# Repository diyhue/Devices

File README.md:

# Devices
DIY Sensors and Controllers with support for diyHue

Documentation and instructions can be found at [diyhue.readthedocs.io](https://diyhue.readthedocs.io/en/latest/AddFuncts/index.html)!

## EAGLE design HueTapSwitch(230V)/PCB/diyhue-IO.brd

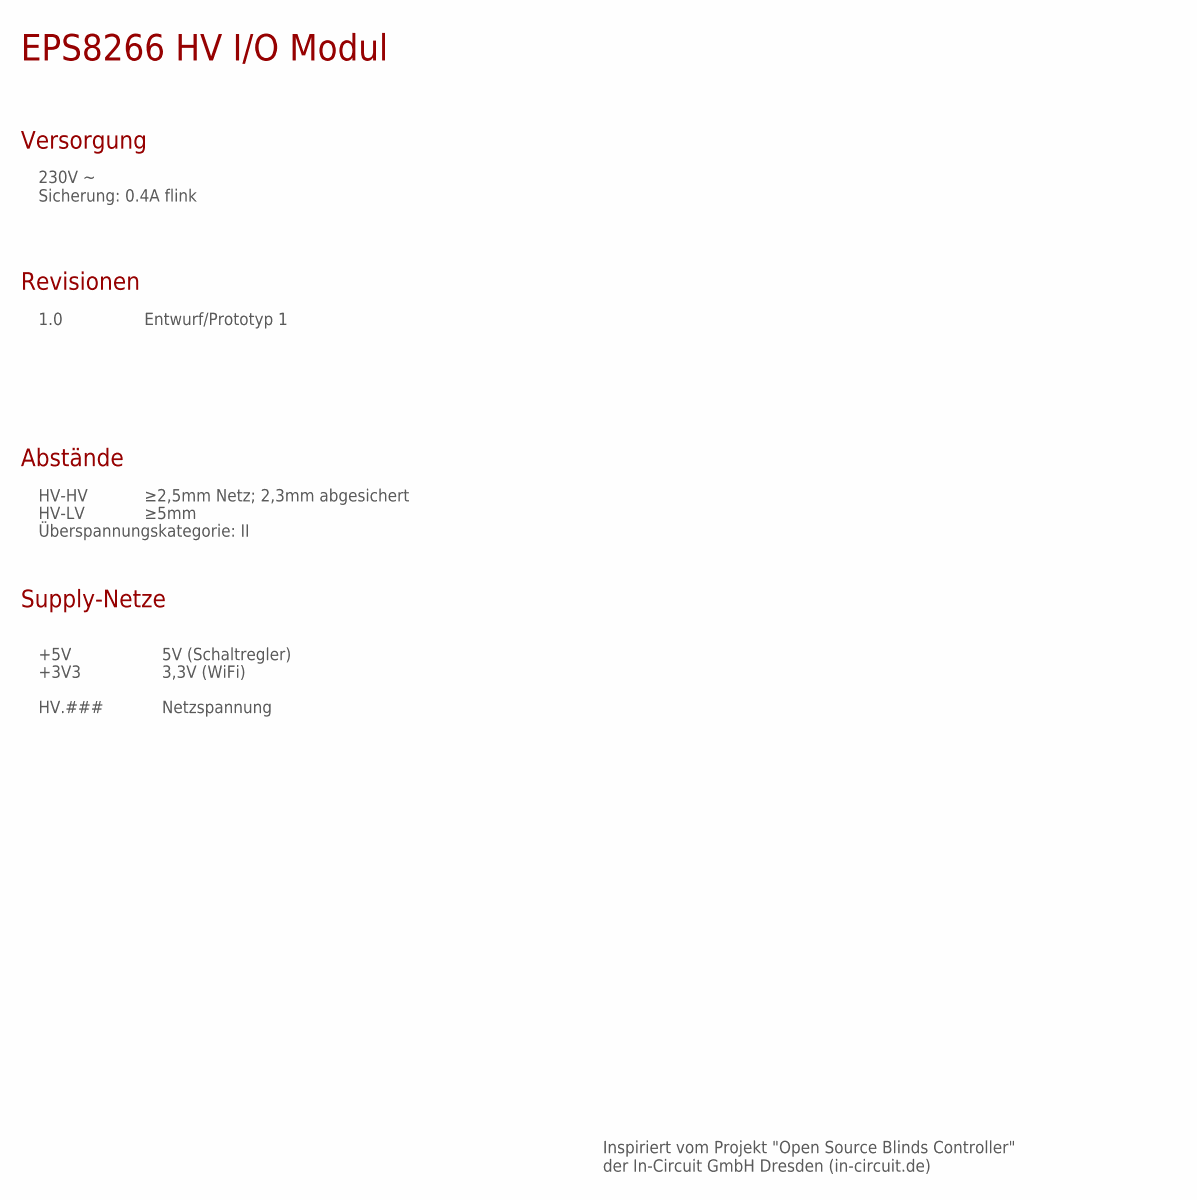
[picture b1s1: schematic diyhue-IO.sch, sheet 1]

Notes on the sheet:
Versorgung
Revisionen
1.0
Entwurf/Prototyp 1
230V ~ Sicherung: 0.4A flink
Supply-Netze
+3V3
+5V
5V (Schaltregler)
3,3V (WiFi)
Inspiriert vom Projekt "Open Source Blinds Controller" der In-Circuit GmbH Dresden (in-circuit.de)
Abstände
HV-HV
HV-LV
≥2,5mm Netz; 2,3mm abgesichert
≥5mm
Überspannungskategorie: II
HV.###
Netzspannung

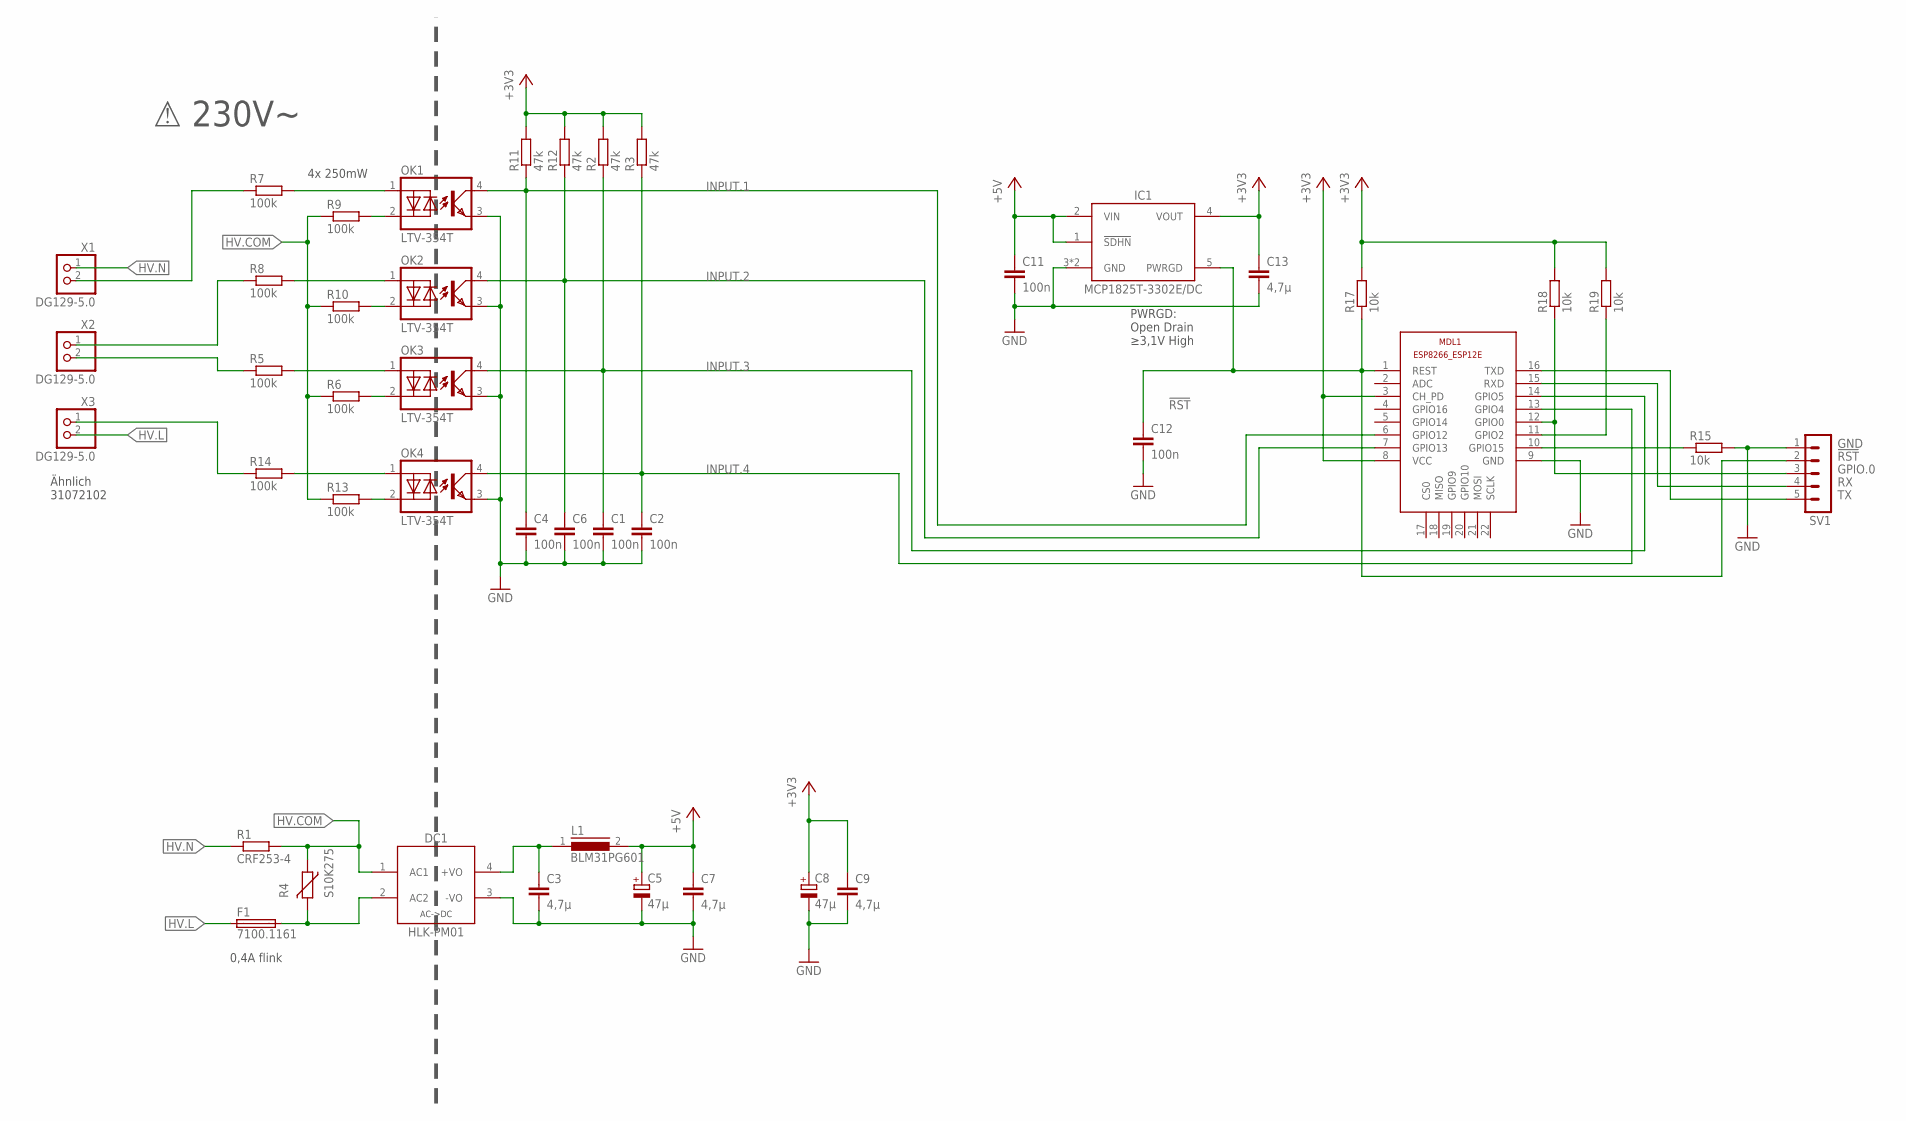
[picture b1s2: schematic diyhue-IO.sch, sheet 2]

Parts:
C1, C2, C4, C6, C11, C12: 100n; C0805K
C3, C7, C9, C13: 4,7µ; C0805K
C5, C8: 47µ; E2-5
DC1: HLK-PM01; HLK_PM01
F1: 7100.1161; SCHURTER_FRT250
IC1: MCP1825T-3302E/DC; SOT-223/5
L1: BLM31PG601; BLM31P
MDL1: ESP8266-12EESP8266-ESP12E; ESP8266-ESP12E
OK1, OK2, OK3, OK4: LTV-354T; LITEON_LTV-354
R1: CRF253-4; 0414V
R2, R3, R11, R12: 47k; R0805W
R4: S10K275; EPCOS_S10K275
R5, R6, R7, R8, R9, R10, R13, R14: 100k; R1210
R15, R17, R18, R19: 10k; R0805W
SV1: MA05-1
X1, X2, X3: DG129-5.0; 31012102

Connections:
!RST: C12.1, IC1.5 (PWRGD), MDL1.1 (REST), R17.1, SV1.2
+3V3: C8.+, C9.1, C13.1, IC1.4 (VOUT), MDL1.3 (CH_PD), MDL1.8 (VCC), R2.2, R3.2, R11.2, R12.2, R17.2, R18.2, R19.2
+5V: C5.+, C7.1, C11.1, IC1.1 (!SDHN), IC1.2 (VIN), L1.2
GND: C1.2, C2.2, C3.2, C4.2, C5.-, C6.2, C7.2, C8.-, C9.2, C11.2, C12.2, C13.2, DC1.3 (-VO), IC1.3 (GND), IC1.6 (GND), MDL1.9 (GND), OK1.3 (E), OK2.3 (E), OK3.3 (E), OK4.3 (E), R15.2, SV1.1
GPIO.0: MDL1.12 (GPIO0), R18.1, SV1.3
GPIO.2: MDL1.11 (GPIO2), R19.1
GPIO.15: MDL1.10 (GPIO15), R15.1
HV.COM: DC1.1 (AC1), R1.2, R4.1, R6.1, R9.1, R10.1, R13.1
HV.IN1: R7.1, X1.2
HV.IN2: R8.1, X2.1
HV.L: F1.1, X3.2
HV.N: R1.1, X1.1
HV.OUT1: R5.1, X2.2
HV.OUT2: R14.1, X3.1
INPUT.1: C4.1, MDL1.6 (GPIO12), OK1.4 (C), R11.1
INPUT.2: C6.1, MDL1.7 (GPIO13), OK2.4 (C), R12.1
INPUT.3: C1.1, MDL1.14 (GPIO5), OK3.4 (C), R2.1
INPUT.4: C2.1, MDL1.13 (GPIO4), OK4.4 (C), R3.1
unnamed: C3.1, DC1.4 (+VO), L1.1
unnamed: DC1.2 (AC2), F1.2, R4.2
unnamed: OK3.2 (CA), R6.2
unnamed: OK4.2 (CA), R13.2
unnamed: OK4.1 (AC), R14.2
unnamed: OK1.2 (CA), R9.2
unnamed: OK2.2 (CA), R10.2
unnamed: OK1.1 (AC), R7.2
unnamed: OK2.1 (AC), R8.2
unnamed: OK3.1 (AC), R5.2
RX: MDL1.15 (RXD), SV1.4
TX: MDL1.16 (TXD), SV1.5

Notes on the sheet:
Ähnlich 31072102
4x 250mW
0,4A flink
⚠ 230V~
PWRGD: Open Drain ≥3,1V High

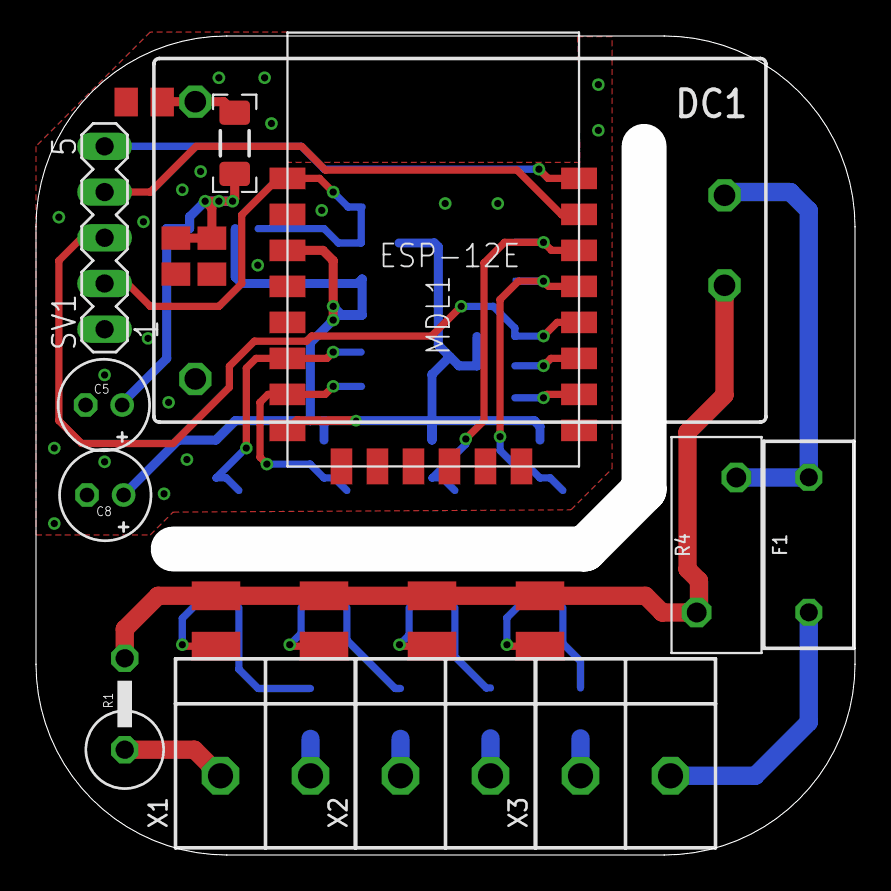
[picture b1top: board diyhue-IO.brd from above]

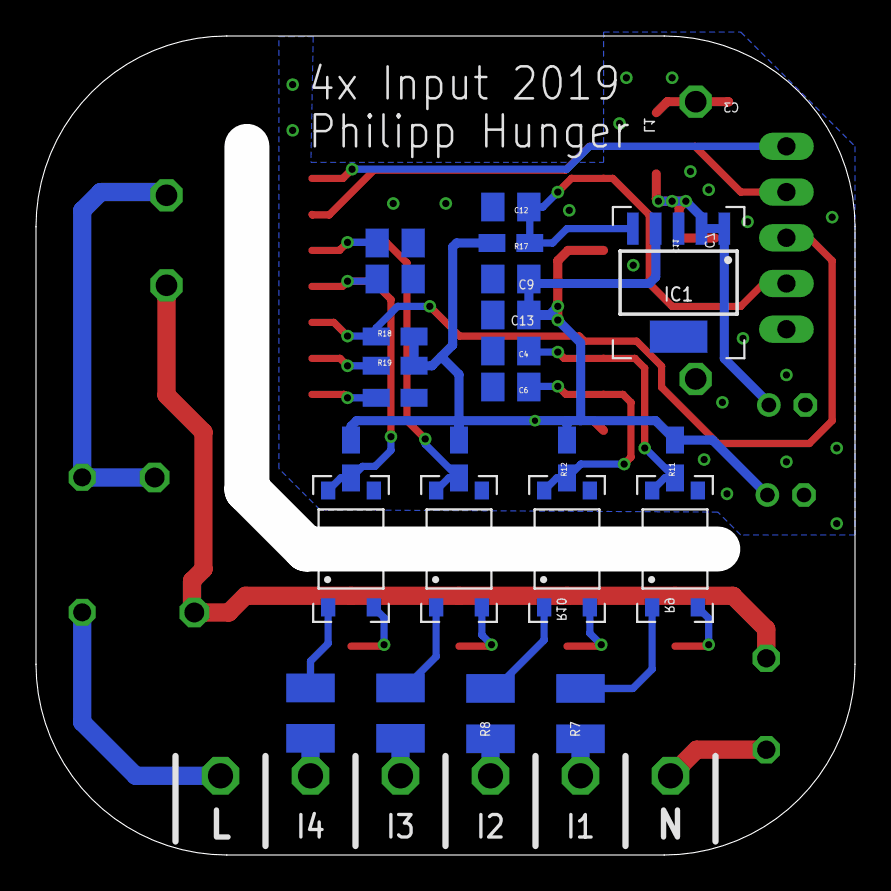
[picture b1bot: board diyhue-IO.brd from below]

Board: 2 copper layers, 45.5 x 45.5 mm, 43 parts (24 on the bottom side), 30 nets.

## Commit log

2017-04-07 Major update, multiple improvements
2017-04-13 beta sketches for tap switch and dimmer switch
2017-04-13 change discover request location
2017-04-15 improved sensor sketches and circuit diagram
2017-05-01 Switch to new python bridge emulator
2017-05-23 support long press dimming codes
2017-06-02 added support for Hue Motion sensor + circuit prototype
2017-06-03 + optimizations for HueMotionSensor
2017-06-10 Added support for controlling lights from other hue bridge devices + minor light improvements + fix issue#8
2017-08-06 new version of motion sensor with anti rf interferences
2017-08-07 add motion sensor README file
2017-09-22 Initial Commit
    A controller for 2 standard wall-switches
2017-10-17 Added WifiManager to Lightswitch
2017-10-17 shrink big size images
2017-10-17 Released V2 of the Switch
    Its now Interrupt-Based wich means faster responding and more
    reliability
2018-09-18 Used defines to enable static IP configuration
    using defines is more user friendly as the user does not have to search for the commented lines
2018-10-31 Entire code was refactored
2018-11-06 added powersave mode
2018-11-06 added new futures present in dimmer switch
2018-11-06 Fix big power consumption in deep sleep
2018-11-06 New version of this sketch
2019-08-09 Switch to new release
2019-08-09 Create test
2019-08-09 correct blinking counter
2019-08-12 change led behaviour to be more discrete
2019-09-29 added 4x Input as Tap Switch
2019-09-30 added 3d printable case
2019-10-01 changed Resistors on the inputs from 0805 to 1210
2019-10-01 added Pictures
2019-11-16 Moved ESP8266 to it's own folder
2019-11-16 ESP32 folder and file
2019-11-16 Added schematic
2019-11-16 Moved info/readme around
2019-11-16 Added small readme

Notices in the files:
HueTapSwitch(230V)/PCB/diyhue-IO.sch:
COPYRIGHT: © 2016 luani.de
LICENSE: CC-BY-SA 4.0
